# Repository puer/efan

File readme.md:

### 电源

stm32f030f4p6 电流 30mA MAX

电源设计 最大 50mA 

5v 50mA 输出 -> AMS1117-3.3

输入 27 最低25

ton/toff = (5+0.8)/(25-0.8-5) = 0.37

f = 50 KHz

20us

toff = 20us / (1+0.37) = 14.6 us

ton(max)  = 5.4us

Ct = ton(max) * 0.4 u = 216pF = 220 pF

Ipk = 50mA * 2 = 100mA

L = 853uH

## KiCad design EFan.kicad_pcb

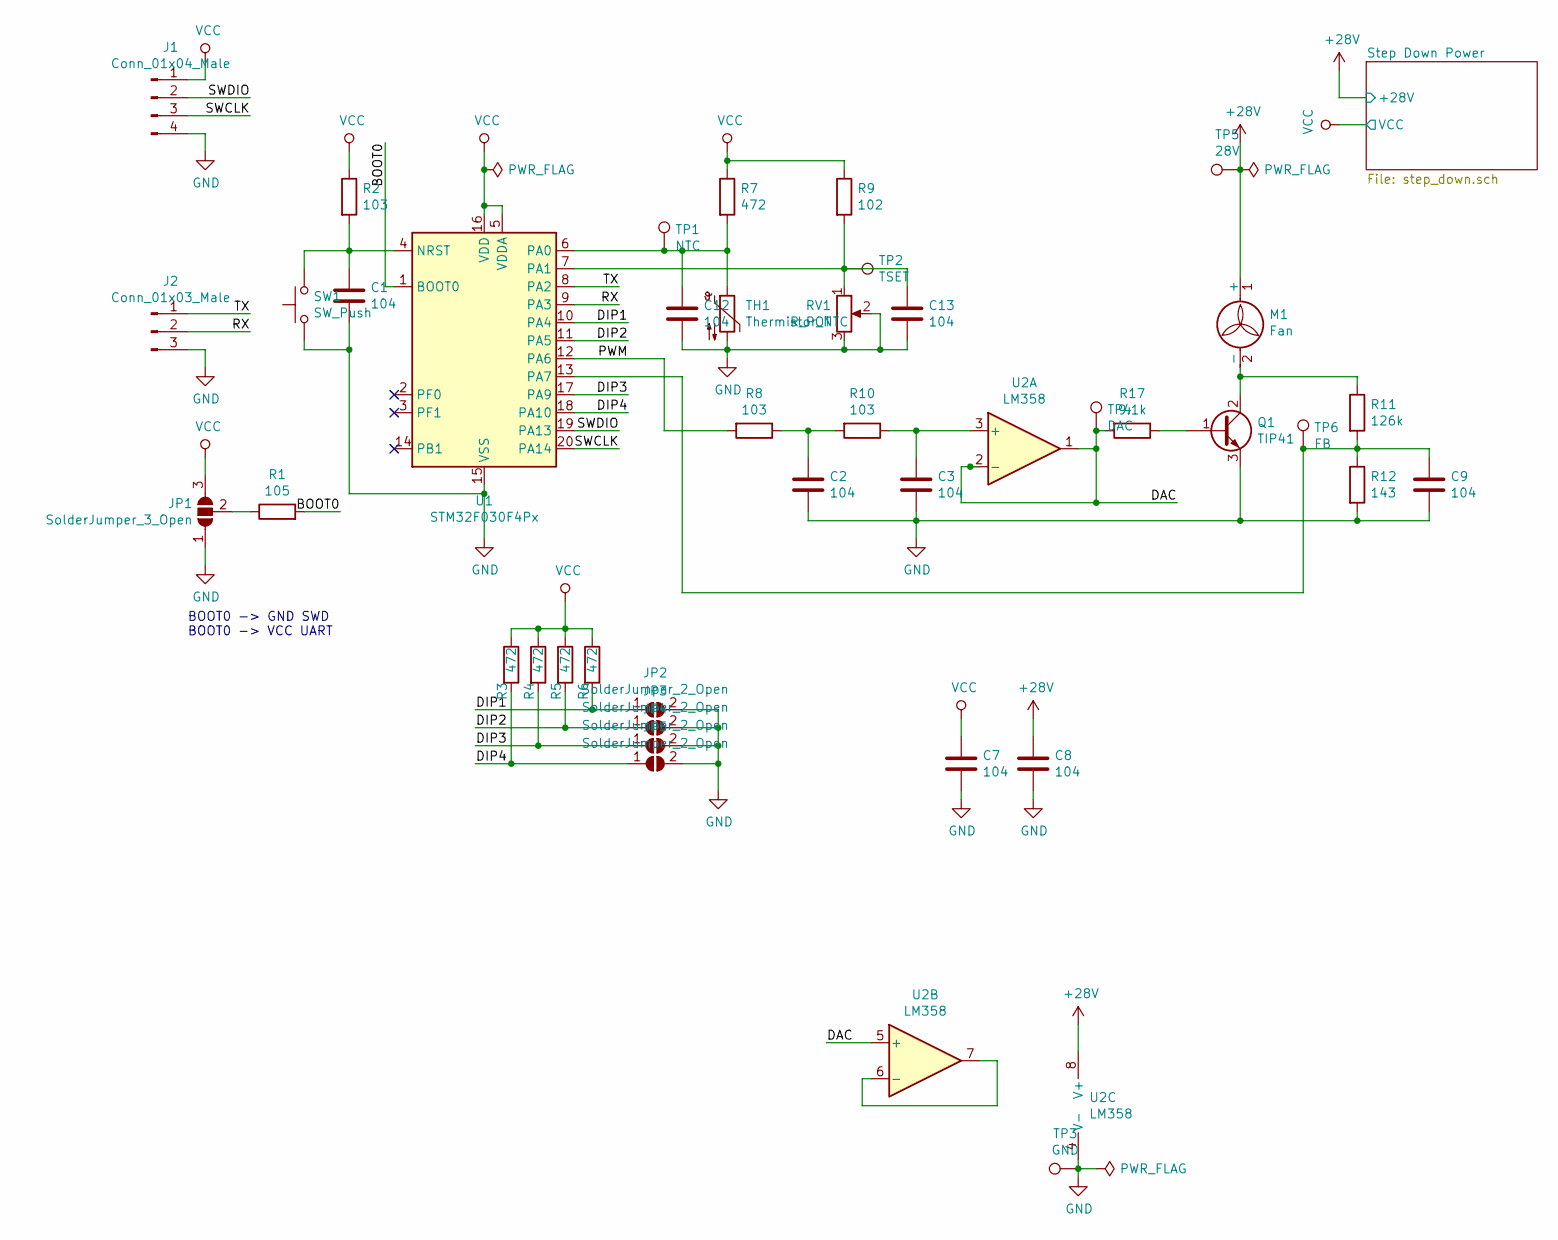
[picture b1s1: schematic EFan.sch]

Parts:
C1, C2, C3, C7, C8, C9, C12, C13: 104; C_0603_1608Metric_Pad1.05x0.95mm_HandSolder
J1: Conn_01x04_Male; PinHeader_1x04_P2.54mm_Vertical
J2: Conn_01x03_Male; PinHeader_1x03_P2.54mm_Vertical
JP1: SolderJumper_3_Open; SolderJumper-3_P1.3mm_Open_RoundedPad1.0x1.5mm_NumberLabels
JP2, JP3, JP4, JP5: SolderJumper_2_Open; SolderJumper-2_P1.3mm_Open_RoundedPad1.0x1.5mm
M1: Fan; PinHeader_1x02_P2.54mm_Vertical
Q1: TIP41; TO-220-3_Vertical
R1: 105; R_0603_1608Metric_Pad1.05x0.95mm_HandSolder
R2, R8, R10: 103; R_0603_1608Metric_Pad1.05x0.95mm_HandSolder
R3, R4, R5, R6, R7: 472; R_0603_1608Metric_Pad1.05x0.95mm_HandSolder
R9: 102; R_0603_1608Metric_Pad1.05x0.95mm_HandSolder
R11: 126k; R_0603_1608Metric_Pad1.05x0.95mm_HandSolder
R12: 143; R_0603_1608Metric_Pad1.05x0.95mm_HandSolder
R17: 9.1k; R_0603_1608Metric_Pad1.05x0.95mm_HandSolder
RV1: R_POT; Potentiometer_Bourns_3296W_Vertical
SW1: SW_Push; SW_PUSH_6mm
TH1: Thermistor_NTC; PinHeader_1x02_P2.54mm_Vertical
TP1: NTC; TestPoint_Loop_D2.50mm_Drill1.0mm
TP2: TSET; TestPoint_Loop_D2.50mm_Drill1.0mm
TP3: GND; PinHeader_1x01_P2.54mm_Vertical
TP4: DAC; TestPoint_Loop_D2.50mm_Drill1.0mm
TP5: 28V; PinHeader_1x01_P2.54mm_Vertical
TP6: FB; TestPoint_Loop_D2.50mm_Drill1.0mm
U1: STM32F030F4Px; TSSOP-20_4.4x6.5mm_P0.65mm
U2: LM358; DIP-8_W7.62mm

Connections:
+28V: C8.1, M1.1 (+), TP5.1, U2.8 (V+); also elsewhere on the board
/BOOT0: R1.2, U1.1 (BOOT0)
/DAC: R17.2, TP4.1, U2.1, U2.2 (-), U2.5 (+)
/DIP1: JP2.1 (A), R6.2, U1.10 (PA4)
/DIP2: JP3.1 (A), R5.2, U1.11 (PA5)
/DIP3: JP4.1 (A), R4.2, U1.17 (PA9)
/DIP4: JP5.1 (A), R3.2, U1.18 (PA10)
/PWM: R8.2, U1.12 (PA6)
/RX: J2.2, U1.9 (PA3)
/SWCLK: J1.3, U1.20 (PA14)
/SWDIO: J1.2, U1.19 (PA13)
/TX: J2.1, U1.8 (PA2)
GND: C1.2, C2.2, C3.2, C7.2, C8.2, C9.2, C12.2, C13.2, J1.4, J2.3, JP1.1 (A), JP2.2 (B), JP3.2 (B), JP4.2 (B), JP5.2 (B), Q1.3 (E), R12.2, RV1.2, RV1.3, SW1.1, TH1.2, TP3.1, U1.15 (VSS), U2.4 (V-); also elsewhere on the board
unnamed: C1.1, R2.2, SW1.2, U1.4 (NRST)
unnamed: C2.1, R8.1, R10.2
unnamed: C3.1, R10.1, U2.3 (+)
unnamed: C9.1, R11.2, R12.1, TP6.1, U1.13 (PA7)
unnamed: C12.1, R7.2, TH1.1, TP1.1, U1.6 (PA0)
unnamed: C13.1, R9.2, RV1.1, TP2.1, U1.7 (PA1)
unnamed: JP1.2 (C), R1.1
unnamed: M1.2 (-), Q1.2 (C), R11.1
unnamed: Q1.1 (B), R17.1
unnamed: U2.6 (-), U2.7
VCC: C7.1, J1.1, JP1.3 (B), R2.1, R3.1, R4.1, R5.1, R6.1, R7.1, R9.1, U1.5 (VDDA), U1.16 (VDD); also elsewhere on the board

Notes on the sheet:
BOOT0 -> GND SWD BOOT0 -> VCC UART

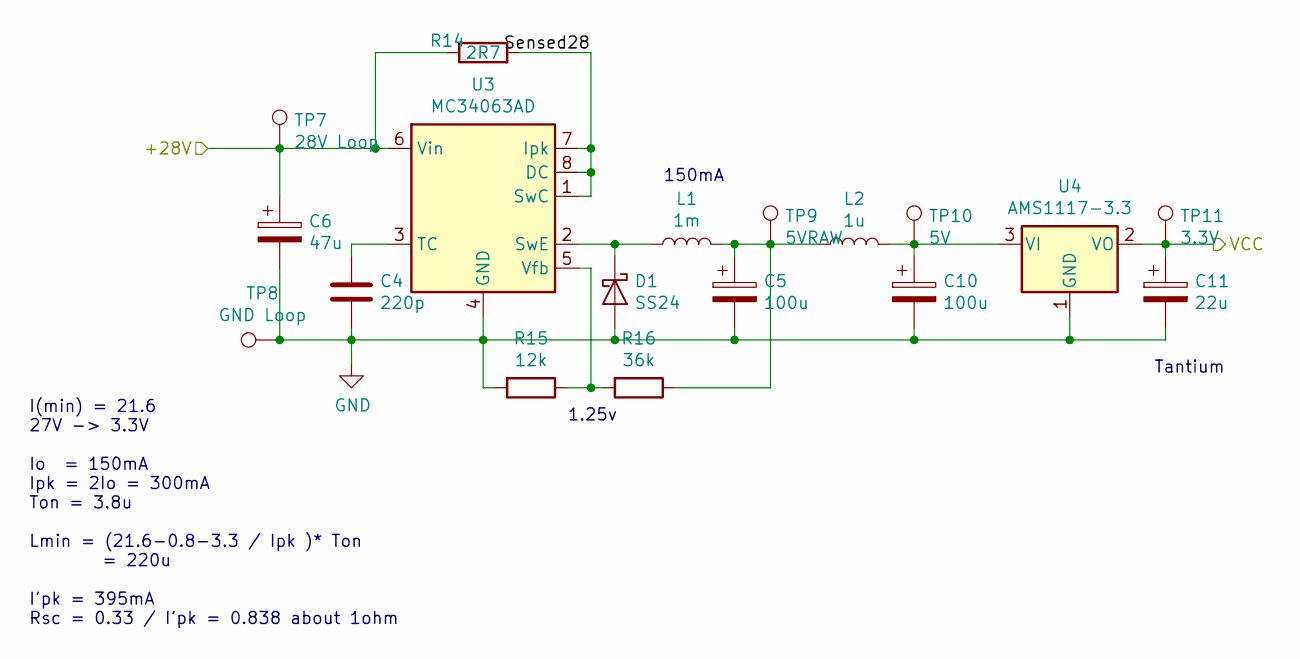
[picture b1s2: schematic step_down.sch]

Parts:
C4: 220p; C_0603_1608Metric_Pad1.05x0.95mm_HandSolder
C5, C10: 100u; C_Radial_D5.0mm_H7.0mm_P2.00mm
C6: 47u; CP_Elec_6.3x5.4
C11: 22u; CP_EIA-3216-18_Kemet-A_Pad1.58x1.35mm_HandSolder
D1: SS24; D_SMA_Handsoldering
L1: 1m; L_Radial_D7.0mm_P3.00mm
L2: 1u; L_0805_2012Metric_Pad1.15x1.40mm_HandSolder
R14: 2R7; R_0603_1608Metric_Pad1.05x0.95mm_HandSolder
R15: 12k; R_0603_1608Metric_Pad1.05x0.95mm_HandSolder
R16: 36k; R_0603_1608Metric_Pad1.05x0.95mm_HandSolder
TP7: 28V Loop; TestPoint_Loop_D2.50mm_Drill1.0mm
TP8: GND Loop; TestPoint_Loop_D2.50mm_Drill1.0mm
TP9: 5VRAW; TestPoint_Loop_D2.50mm_Drill1.0mm
TP10: 5V; TestPoint_Loop_D2.50mm_Drill1.0mm
TP11: 3.3V; TestPoint_Loop_D2.50mm_Drill1.0mm
U3: MC34063AD; SOIC-8_3.9x4.9mm_P1.27mm
U4: AMS1117-3.3; SOT-223-3_TabPin2

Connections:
+28V: C6.1, R14.1, TP7.1, U3.6 (Vin); also elsewhere on the board
/Step Down Power/Sensed28: R14.2, U3.1 (SwC), U3.7 (Ipk), U3.8 (DC)
GND: C4.2, C5.2, C6.2, C10.2, C11.2, D1.2 (A), R15.2, TP8.1, U3.4 (GND), U4.1 (GND); also elsewhere on the board
unnamed: C4.1, U3.3 (TC)
unnamed: C5.1, L1.2, L2.1, R16.1, TP9.1
unnamed: C10.1, L2.2, TP10.1, U4.3 (VI)
unnamed: D1.1 (K), L1.1, U3.2 (SwE)
unnamed: R15.1, R16.2, U3.5 (Vfb)
VCC: C11.1, TP11.1, U4.2 (VO); also elsewhere on the board

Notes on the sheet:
I(min) = 21.6 27V -> 3.3V Io = 150mA Ipk = 2Io = 300mA Ton = 3.8u Lmin = (21.6-0.8-3.3 / Ipk )* Ton = 220u I'pk = 395mA Rsc = 0.33 / I'pk = 0.838 about 1ohm
150mA
1.25v
Tantium

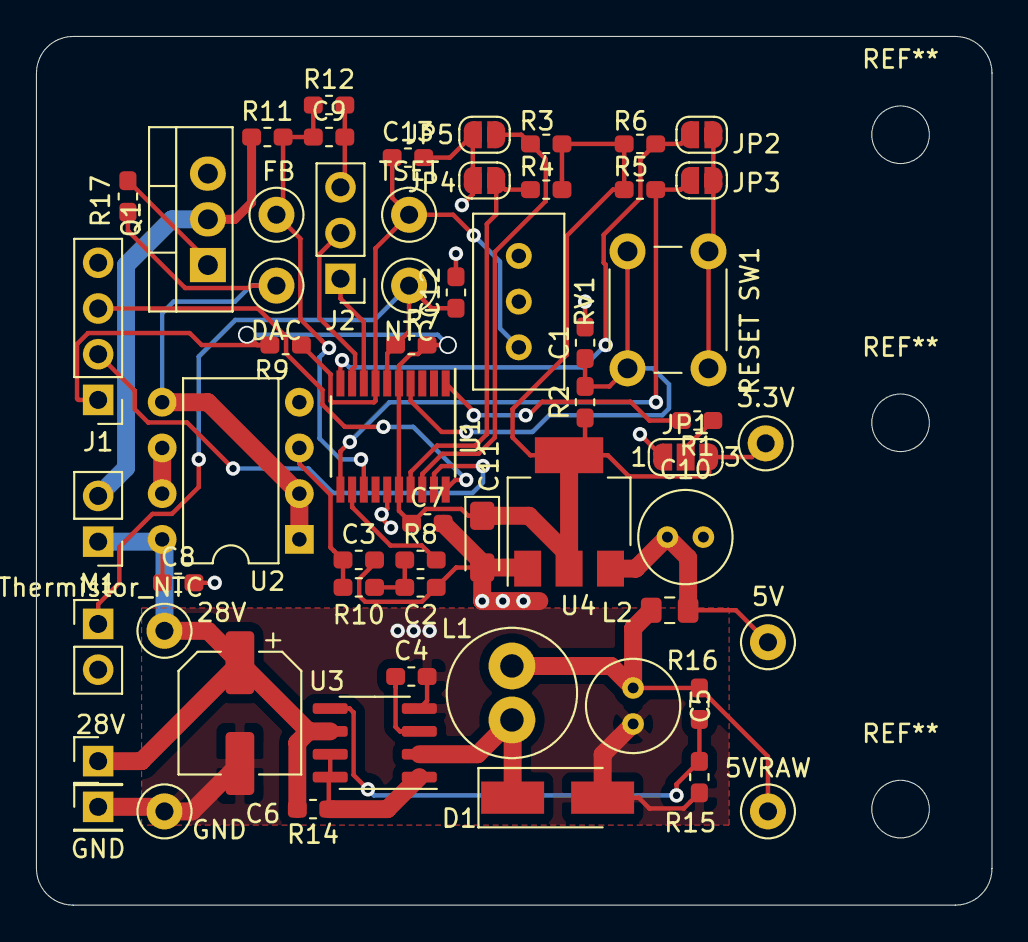
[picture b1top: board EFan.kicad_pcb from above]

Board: 2 copper layers, 53.1 x 48.3 mm, 59 parts (0 on the bottom side), 30 nets.

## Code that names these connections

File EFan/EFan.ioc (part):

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Mcu.Name=STM32F030F4Px
Mcu.Package=TSSOP20
Mcu.UserName=STM32F030F4Px
PA0.Mode=IN0
PA0.Signal=ADC_IN0
PA1.Mode=IN1
PA1.Signal=ADC_IN1
PA13.Mode=Serial_Wire
PA13.Signal=SYS_SWDIO
PA14.Mode=Serial_Wire
PA14.Signal=SYS_SWCLK
PA2.Mode=Asynchronous
PA2.Signal=USART1_TX
PA3.Mode=Asynchronous
PA3.Signal=USART1_RX
PA6.Signal=S_TIM3_CH1
PA7.Signal=S_TIM3_CH2
RCC.SYSCLKFreq_VALUE=48000000
RCC.SYSCLKSource=RCC_SYSCLKSOURCE_PLLCLK
board=custom

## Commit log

2019-10-31 init
2019-11-01 refine pcb
2019-11-02 production 2
2019-11-03 incr r9, to limit current usage
2019-11-07 add 2 coupling caps in adc input
2020-12-07 gitignore update
